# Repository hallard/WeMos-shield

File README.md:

Basic ESP8266 WeMos Shield
==========================

This shield is used to quickly do some tests/boards with WeMos ESP8266 boards it has just few minimal features.
- I2C Pullups placement
- Classic I2C 128x64 OLED connector (with PAD to reverse 3V3 and GND if needed)
- pad to solder components if needed to
- N-FET placement for 1 signal adapter such as 5V to 3V3

New in Version 1.1
- I2C connector has PAD to reverse 3V3 and GND if needed
- Ground Plane has isolate of 8mil to avoid in some case shorts when soldering

You can find more information on WeMos on their [site][1], it's really well documented.
I now use WeMos boards instead of NodeMCU's one because they're just smaller, features remains the same, but I also suspect WeMos regulator far better quality than the one used on NodeMCU that are just fake of originals AMS117 3V3.

*Boards are ordered as testing from OSHPark, I did not fully tested them yet, I will update as soon has I got them in my hands. Use at your own risks*

Detailed Description
====================

Look at the schematics for more informations.

### Schematic  

### Boards  
&nbsp;
&nbsp; 

You can order the PCB of this board v1.0 at [OSHPARK][3] or V1.1 at [PCBs.io][4]. 
PCBs.io give me some reward when you order my designed boards from their site. This is pretty good, because I can use these rewards to create and design new boards and order boards for a discounted price, so if you don't care about PCB manufacturer please use PCBs.io.

### Assembled boards

I'm currently waiting for boards from OSHPARK

##License

This work is licensed under a [Creative Commons Attribution-NonCommercial 4.0 International License](http://creativecommons.org/licenses/by-nc/4.0/)    

##Misc
See news and other projects on my [blog][2] 
 
[1]: http://www.wemos.cc/wiki/doku.php?id=en:d1_mini
[2]: https://hallard.me
[3]: https://oshpark.com/shared_projects/rnk2lmmh
[4]: https://PCBs.io/share/zZAJY

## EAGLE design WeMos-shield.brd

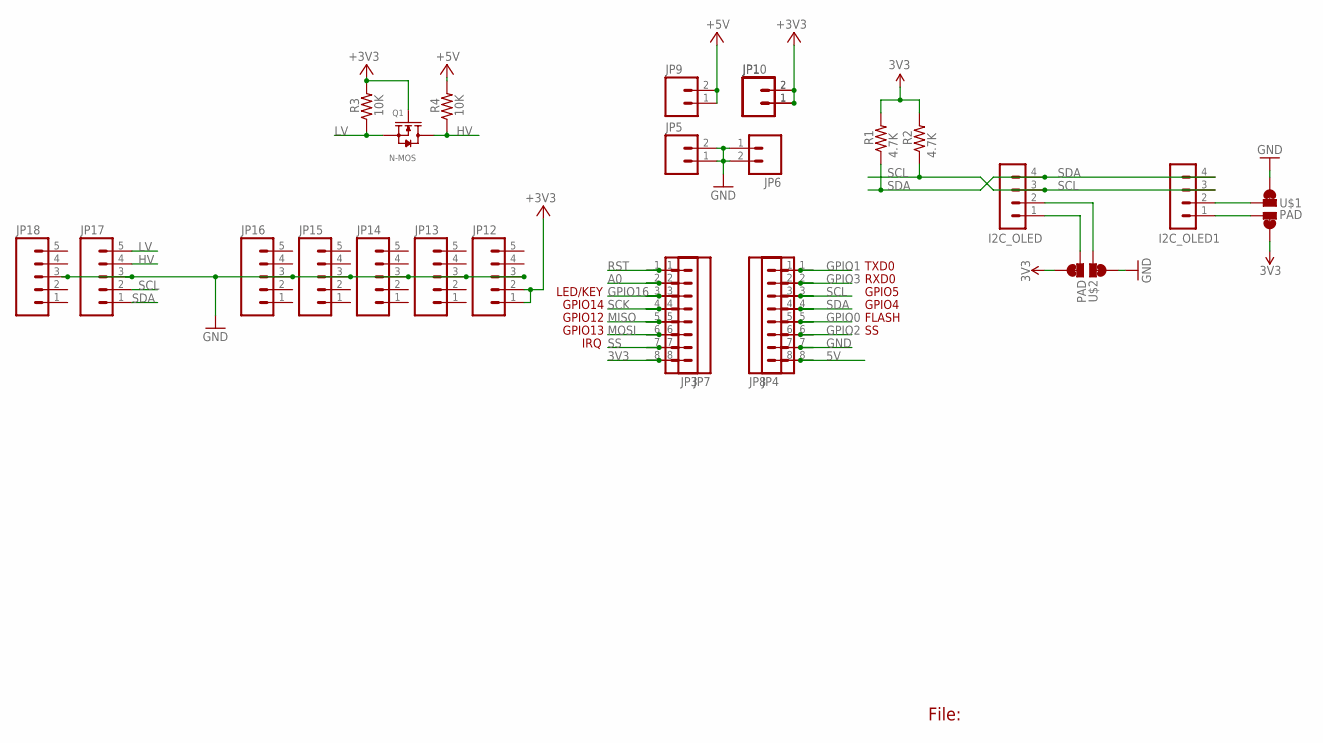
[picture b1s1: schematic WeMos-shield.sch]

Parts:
I2C_OLED, I2C_OLED1: CON_HEADER_1X04'SMALL''; M1X4
JP1, JP5, JP6, JP9, JP10: M021X02_NO_SILK; 1X02_NO_SILK
JP3, JP4, JP7, JP8: M08NO_SILK_FEMALE_PTH; 1X08_NO_SILK
JP12, JP13, JP14, JP15, JP16, JP17, JP18: M05NO_SILK; 1X05_NO_SILK
Q1: N-MOS; SOT23
R1, R2: 4.7K; 0805-RES
R3, R4: 10K; 0805-RES
U$1, U$2: PAD; PAD-JUMPER-SWAP

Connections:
3V3: JP1.1, JP1.2, JP3.8, JP7.8, JP10.1, JP10.2, JP12.1, JP12.2, Q1.1 (G), R1.2, R2.2, R3.2, U$1.4, U$1.44 (4), U$2.4, U$2.44 (4)
5V: JP4.8, JP8.8, JP9.1, JP9.2, R4.2
A0: JP3.2, JP7.2
GND: JP4.7, JP5.1, JP5.2, JP6.1, JP6.2, JP8.7, JP12.3, JP13.3, JP14.3, JP15.3, JP16.3, JP17.3, JP18.3, U$1.1, U$1.11 (1), U$2.1, U$2.11 (1)
GPIO0: JP4.5, JP8.5
GPIO1: JP4.1, JP8.1
GPIO2: JP4.6, JP8.6
GPIO3: JP4.2, JP8.2
GPIO16: JP3.3, JP7.3
HV: JP17.4, Q1.3 (D), R4.1
LV: JP17.5, Q1.2 (S), R3.1
MISO: JP3.5, JP7.5
MOSI: JP3.6, JP7.6
RST: JP3.1, JP7.1
SCK: JP3.4, JP7.4
SCL: I2C_OLED.3, I2C_OLED1.3, JP4.3, JP8.3, JP17.2, R2.1
SDA: I2C_OLED.4, I2C_OLED1.4, JP4.4, JP8.4, JP17.1, R1.1
SS: JP3.7, JP7.7
V+J: I2C_OLED.1, U$2.3
V+O: I2C_OLED1.1, U$1.3
V-J: I2C_OLED.2, U$2.2
V-O: I2C_OLED1.2, U$1.2

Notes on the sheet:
File:
FLASH
GPIO12
GPIO4
GPIO5
RXD0
TXD0
GPIO13
GPIO14
IRQ
LED/KEY

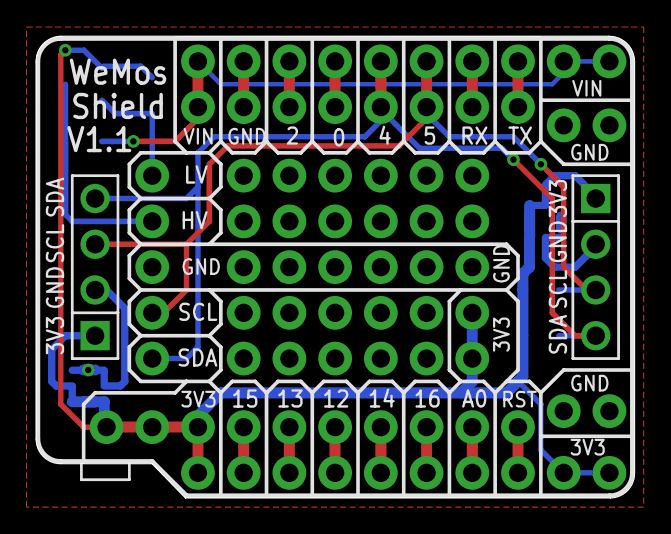
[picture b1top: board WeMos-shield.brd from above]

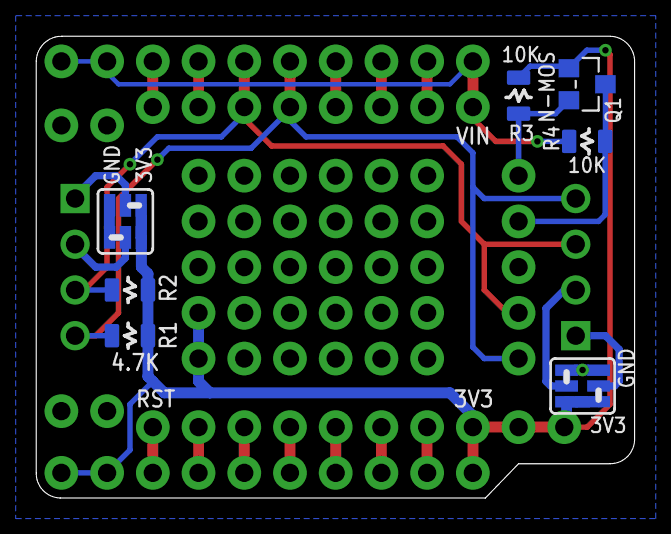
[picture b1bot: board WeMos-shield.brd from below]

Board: 2 copper layers, 33.2 x 25.7 mm, 25 parts (7 on the bottom side), 22 nets.

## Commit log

2016-01-16 Creation
2016-01-16 Added OSHPark link
2017-06-19 Version 1.1

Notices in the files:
parts and their libraries:
SparkFun-Connectors: Licensing: Creative Commons ShareAlike 4.0 International - https://creativecommons.org/licenses/by-sa/4.0
